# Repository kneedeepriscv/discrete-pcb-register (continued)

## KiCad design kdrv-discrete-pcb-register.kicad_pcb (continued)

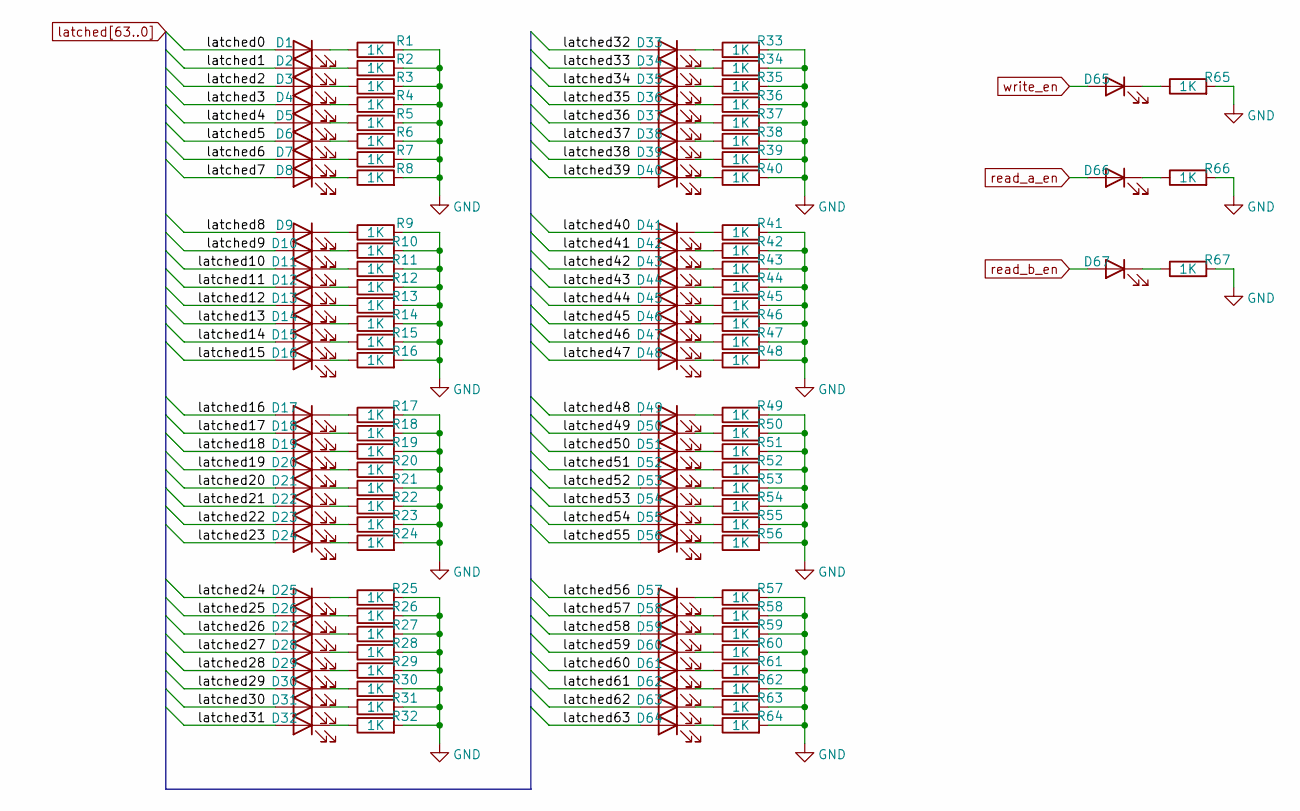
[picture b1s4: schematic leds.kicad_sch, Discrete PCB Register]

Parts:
D1: LED 0603 0605 0805 Right Angle Yellow Amber Green; LED_0805_2012Metric_Pad1.15x1.40mm_HandSolder
D2, D3, D4, D5, D6, D7, D8, D9, D10, D11, D12, D13, D14, D15, D16, D17, D18, D19, D20, D21, D22, D23, D24, D25, D26, D27, D28, D29, D30, D31, D32, D33, D34, D35, D36, D37, D38, D39, D40, D41, D42, D43, D44, D45, D46, D47, D48, D49, D50, D51, D52, D53, D54, D55, D56, D57, D58, D59, D60, D61, D62, D63, D64, D65, D66, D67: LED; LED_0805_2012Metric_Pad1.15x1.40mm_HandSolder
R1, R2, R3, R4, R5, R6, R7, R8, R9, R10, R11, R12, R13, R14, R15, R16, R17, R18, R19, R20, R21, R22, R23, R24, R25, R26, R27, R28, R29, R30, R31, R32, R33, R34, R35, R36, R37, R38, R39, R40, R41, R42, R43, R44, R45, R46, R47, R48, R49, R50, R51, R52, R53, R54, R55, R56, R57, R58, R59, R60, R61, R62, R63, R64, R65, R66, R67: 1K; R_0805_2012Metric_Pad1.20x1.40mm_HandSolder

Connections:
GND: R1.2, R2.2, R3.2, R4.2, R5.2, R6.2, R7.2, R8.2, R9.2, R10.2, R11.2, R12.2, R13.2, R14.2, R15.2, R16.2, R17.2, R18.2, R19.2, R20.2, R21.2, R22.2, R23.2, R24.2, R25.2, R26.2, R27.2, R28.2, R29.2, R30.2, R31.2, R32.2, R33.2, R34.2, R35.2, R36.2, R37.2, R38.2, R39.2, R40.2, R41.2, R42.2, R43.2, R44.2, R45.2, R46.2, R47.2, R48.2, R49.2, R50.2, R51.2, R52.2, R53.2, R54.2, R55.2, R56.2, R57.2, R58.2, R59.2, R60.2, R61.2, R62.2, R63.2, R64.2, R65.2, R66.2, R67.2; also elsewhere on the board
unnamed: D1.1 (K), R1.1
unnamed: D2.1 (K), R2.1
unnamed: D3.1 (K), R3.1
unnamed: D4.1 (K), R4.1
unnamed: D5.1 (K), R5.1
unnamed: D6.1 (K), R6.1
unnamed: D7.1 (K), R7.1
unnamed: D8.1 (K), R8.1
unnamed: D9.1 (K), R9.1
unnamed: D10.1 (K), R10.1
unnamed: D11.1 (K), R11.1
unnamed: D12.1 (K), R12.1
unnamed: D13.1 (K), R13.1
unnamed: D14.1 (K), R14.1
unnamed: D15.1 (K), R15.1
unnamed: D16.1 (K), R16.1
unnamed: D17.1 (K), R17.1
unnamed: D18.1 (K), R18.1
unnamed: D19.1 (K), R19.1
unnamed: D20.1 (K), R20.1
unnamed: D21.1 (K), R21.1
unnamed: D22.1 (K), R22.1
unnamed: D23.1 (K), R23.1
unnamed: D24.1 (K), R24.1
unnamed: D25.1 (K), R25.1
unnamed: D26.1 (K), R26.1
unnamed: D27.1 (K), R27.1
unnamed: D28.1 (K), R28.1
unnamed: D29.1 (K), R29.1
unnamed: D30.1 (K), R30.1
unnamed: D31.1 (K), R31.1
unnamed: D32.1 (K), R32.1
unnamed: D33.1 (K), R33.1
unnamed: D34.1 (K), R34.1
unnamed: D35.1 (K), R35.1
unnamed: D36.1 (K), R36.1
unnamed: D37.1 (K), R37.1
unnamed: D38.1 (K), R38.1
unnamed: D39.1 (K), R39.1
unnamed: D40.1 (K), R40.1
unnamed: D41.1 (K), R41.1
unnamed: D42.1 (K), R42.1
unnamed: D43.1 (K), R43.1
unnamed: D44.1 (K), R44.1
unnamed: D45.1 (K), R45.1
unnamed: D46.1 (K), R46.1
unnamed: D47.1 (K), R47.1
unnamed: D48.1 (K), R48.1
unnamed: D49.1 (K), R49.1
unnamed: D50.1 (K), R50.1
unnamed: D51.1 (K), R51.1
unnamed: D52.1 (K), R52.1
unnamed: D53.1 (K), R53.1
unnamed: D54.1 (K), R54.1
unnamed: D55.1 (K), R55.1
unnamed: D56.1 (K), R56.1
unnamed: D57.1 (K), R57.1
unnamed: D58.1 (K), R58.1
unnamed: D59.1 (K), R59.1
unnamed: D60.1 (K), R60.1
unnamed: D61.1 (K), R61.1
unnamed: D62.1 (K), R62.1
unnamed: D63.1 (K), R63.1
unnamed: D64.1 (K), R64.1
unnamed: D65.1 (K), R65.1
unnamed: D66.1 (K), R66.1
unnamed: D67.1 (K), R67.1
latched0: D1.2 (A); also elsewhere on the board
latched1: D2.2 (A); also elsewhere on the board
latched2: D3.2 (A); also elsewhere on the board
latched3: D4.2 (A); also elsewhere on the board
latched4: D5.2 (A); also elsewhere on the board
latched5: D6.2 (A); also elsewhere on the board
latched6: D7.2 (A); also elsewhere on the board
latched7: D8.2 (A); also elsewhere on the board
latched8: D9.2 (A); also elsewhere on the board
latched9: D10.2 (A); also elsewhere on the board
latched10: D11.2 (A); also elsewhere on the board
latched11: D12.2 (A); also elsewhere on the board
latched12: D13.2 (A); also elsewhere on the board
latched13: D14.2 (A); also elsewhere on the board
latched14: D15.2 (A); also elsewhere on the board
latched15: D16.2 (A); also elsewhere on the board
latched16: D17.2 (A); also elsewhere on the board
latched17: D18.2 (A); also elsewhere on the board
latched18: D19.2 (A); also elsewhere on the board
latched19: D20.2 (A); also elsewhere on the board
latched20: D21.2 (A); also elsewhere on the board
latched21: D22.2 (A); also elsewhere on the board
latched22: D23.2 (A); also elsewhere on the board
latched23: D24.2 (A); also elsewhere on the board
latched24: D25.2 (A); also elsewhere on the board
latched25: D26.2 (A); also elsewhere on the board
latched26: D27.2 (A); also elsewhere on the board
latched27: D28.2 (A); also elsewhere on the board
latched28: D29.2 (A); also elsewhere on the board
latched29: D30.2 (A); also elsewhere on the board
latched30: D31.2 (A); also elsewhere on the board
latched31: D32.2 (A); also elsewhere on the board
latched32: D33.2 (A); also elsewhere on the board
latched33: D34.2 (A); also elsewhere on the board
latched34: D35.2 (A); also elsewhere on the board
latched35: D36.2 (A); also elsewhere on the board
latched36: D37.2 (A); also elsewhere on the board
latched37: D38.2 (A); also elsewhere on the board
latched38: D39.2 (A); also elsewhere on the board
latched39: D40.2 (A); also elsewhere on the board
latched40: D41.2 (A); also elsewhere on the board
latched41: D42.2 (A); also elsewhere on the board
latched42: D43.2 (A); also elsewhere on the board
latched43: D44.2 (A); also elsewhere on the board
latched44: D45.2 (A); also elsewhere on the board
latched45: D46.2 (A); also elsewhere on the board
latched46: D47.2 (A); also elsewhere on the board
latched47: D48.2 (A); also elsewhere on the board
latched48: D49.2 (A); also elsewhere on the board
latched49: D50.2 (A); also elsewhere on the board
latched50: D51.2 (A); also elsewhere on the board
latched51: D52.2 (A); also elsewhere on the board
latched52: D53.2 (A); also elsewhere on the board
latched53: D54.2 (A); also elsewhere on the board
latched54: D55.2 (A); also elsewhere on the board
latched55: D56.2 (A); also elsewhere on the board
latched56: D57.2 (A); also elsewhere on the board
latched57: D58.2 (A); also elsewhere on the board
latched58: D59.2 (A); also elsewhere on the board
latched59: D60.2 (A); also elsewhere on the board
latched60: D61.2 (A); also elsewhere on the board
latched61: D62.2 (A); also elsewhere on the board
latched62: D63.2 (A); also elsewhere on the board
latched63: D64.2 (A); also elsewhere on the board
read_a_en: D66.2 (A); also elsewhere on the board
read_b_en: D67.2 (A); also elsewhere on the board
write_en: D65.2 (A); also elsewhere on the board

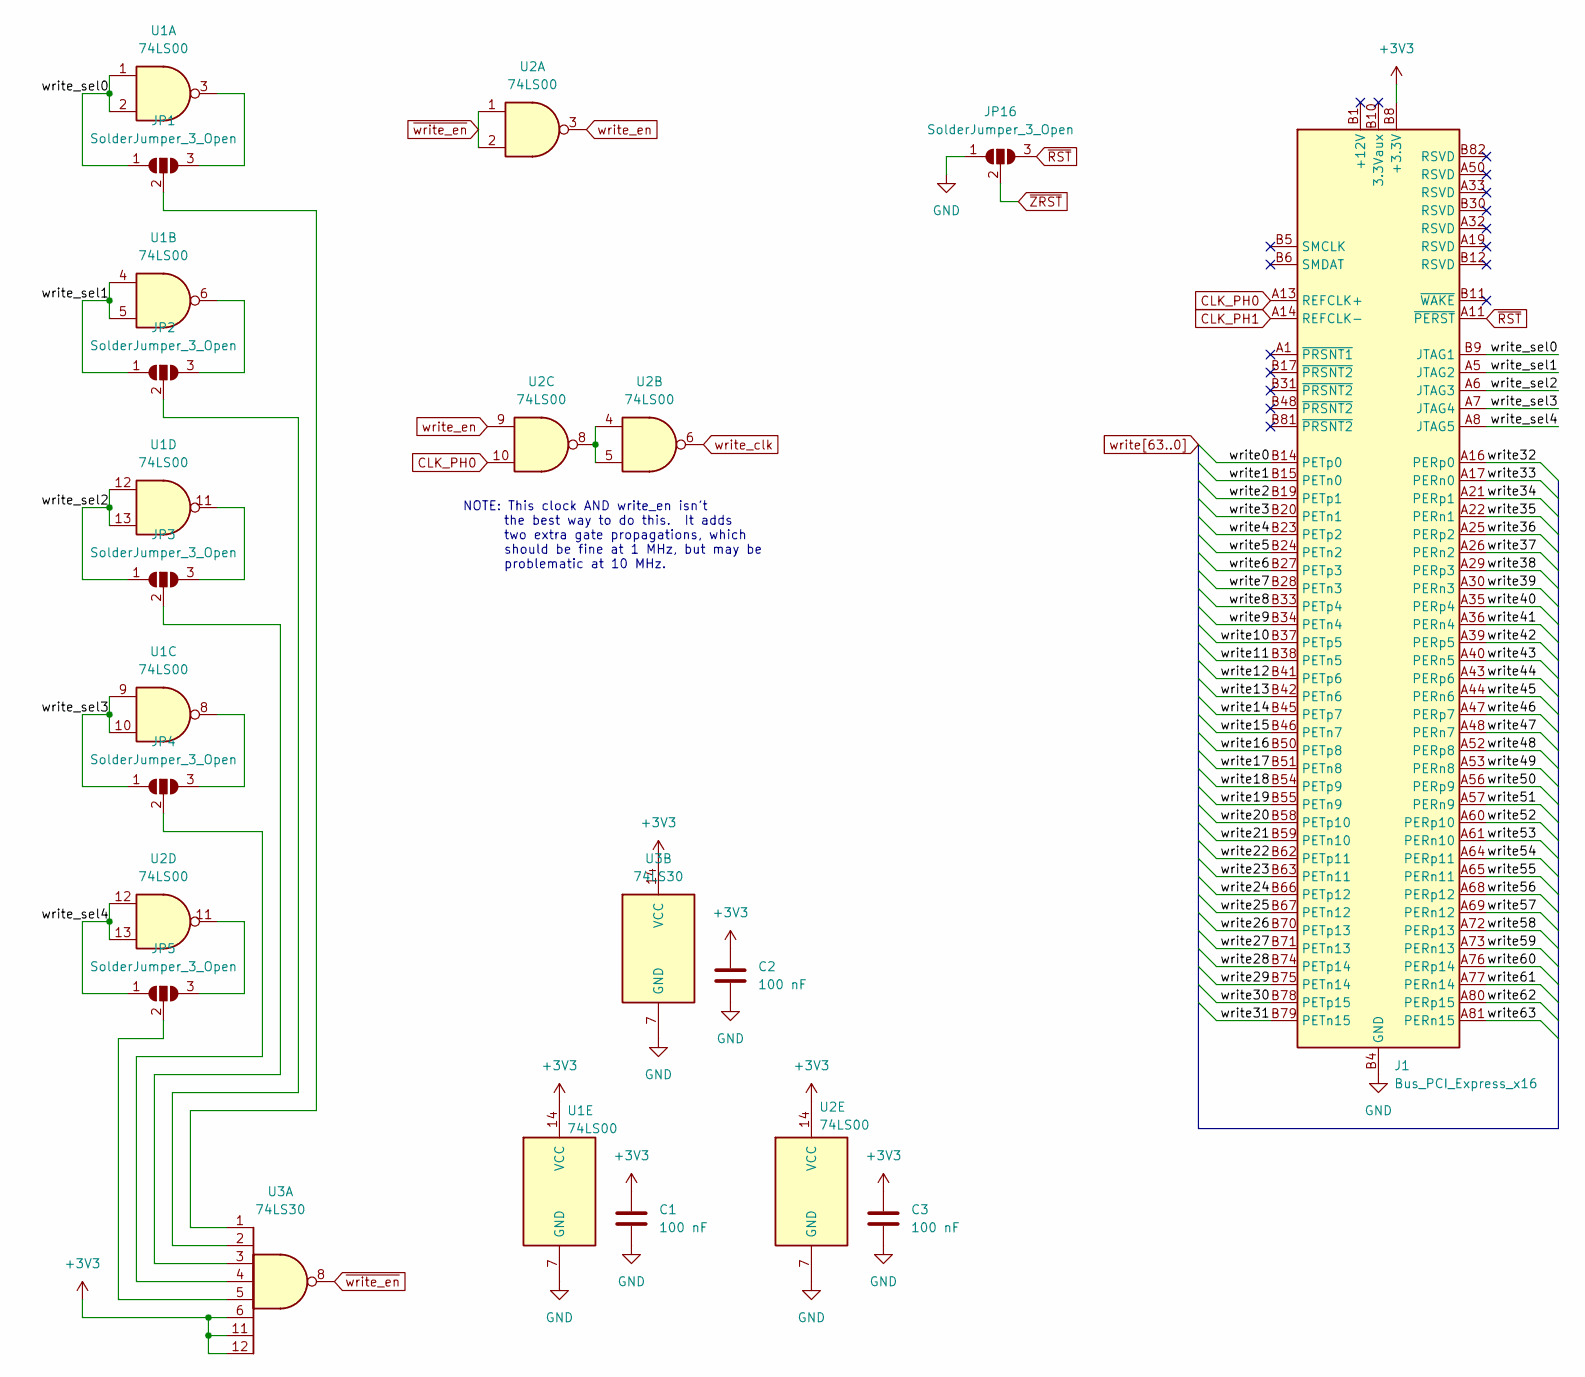
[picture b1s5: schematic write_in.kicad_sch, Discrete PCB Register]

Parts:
C1, C2, C3: 100 nF; C_0805_2012Metric_Pad1.18x1.45mm_HandSolder
J1: Bus_PCI_Express_x16; BUS_PCIexpress_x16
JP1, JP2, JP3, JP4, JP5, JP16: SolderJumper_3_Open; SolderJumper-3_P1.3mm_Open_RoundedPad1.0x1.5mm
U1, U2: 74LS00; SOIC-14_3.9x8.7mm_P1.27mm
U3: 74LS30; SOIC-14_3.9x8.7mm_P1.27mm

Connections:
+3V3: C1.1, C2.1, C3.1, J1.A9 (+3.3V), J1.A10 (+3.3V), J1.B8 (+3.3V), U1.14 (VCC), U2.14 (VCC), U3.6, U3.11, U3.12, U3.14 (VCC); also elsewhere on the board
/Write In/write_sel0: J1.B9 (JTAG1), JP1.1 (A), U1.1, U1.2
/Write In/write_sel1: J1.A5 (JTAG2), JP2.1 (A), U1.4, U1.5
/Write In/write_sel2: J1.A6 (JTAG3), JP3.1 (A), U1.12, U1.13
/Write In/write_sel3: J1.A7 (JTAG4), JP4.1 (A), U1.9, U1.10
/Write In/write_sel4: J1.A8 (JTAG5), JP5.1 (A), U2.12, U2.13
CLK_PH0: J1.A13 (REFCLK+), U2.10
CLK_PH1: J1.A14 (REFCLK-)
GND: C1.2, C2.2, C3.2, J1.A4 (GND), J1.A12 (GND), J1.A15 (GND), J1.A18 (GND), J1.A20 (GND), J1.A23 (GND), J1.A24 (GND), J1.A27 (GND), J1.A28 (GND), J1.A31 (GND), J1.A34 (GND), J1.A37 (GND), J1.A38 (GND), J1.A41 (GND), J1.A42 (GND), J1.A45 (GND), J1.A46 (GND), J1.A49 (GND), J1.A51 (GND), J1.A54 (GND), J1.A55 (GND), J1.A58 (GND), J1.A59 (GND), J1.A62 (GND), J1.A63 (GND), J1.A66 (GND), J1.A67 (GND), J1.A70 (GND), J1.A71 (GND), J1.A74 (GND), J1.A75 (GND), J1.A78 (GND), J1.A79 (GND), J1.A82 (GND), J1.B4 (GND), J1.B7 (GND), J1.B13 (GND), J1.B16 (GND), J1.B18 (GND), J1.B21 (GND), J1.B22 (GND), J1.B25 (GND), J1.B26 (GND), J1.B29 (GND), J1.B32 (GND), J1.B35 (GND), J1.B36 (GND), J1.B39 (GND), J1.B40 (GND), J1.B43 (GND), J1.B44 (GND), J1.B47 (GND), J1.B49 (GND), J1.B52 (GND), J1.B53 (GND), J1.B56 (GND), J1.B57 (GND), J1.B60 (GND), J1.B61 (GND), J1.B64 (GND), J1.B65 (GND), J1.B68 (GND), J1.B69 (GND), J1.B72 (GND), J1.B73 (GND), J1.B76 (GND), J1.B77 (GND), J1.B80 (GND), JP16.1 (A), U1.7 (GND), U2.7 (GND), U3.7 (GND); also elsewhere on the board
unnamed: JP1.3 (B), U1.3
unnamed: JP1.2 (C), U3.1
unnamed: JP2.3 (B), U1.6
unnamed: JP2.2 (C), U3.2
unnamed: JP3.3 (B), U1.11
unnamed: JP3.2 (C), U3.3
unnamed: JP4.3 (B), U1.8
unnamed: JP4.2 (C), U3.4
unnamed: JP5.3 (B), U2.11
unnamed: JP5.2 (C), U3.5
unnamed: U2.4, U2.5, U2.8
write0: J1.B14 (PETp0); also elsewhere on the board
write1: J1.B15 (PETn0); also elsewhere on the board
write2: J1.B19 (PETp1); also elsewhere on the board
write3: J1.B20 (PETn1); also elsewhere on the board
write4: J1.B23 (PETp2); also elsewhere on the board
write5: J1.B24 (PETn2); also elsewhere on the board
write6: J1.B27 (PETp3); also elsewhere on the board
write7: J1.B28 (PETn3); also elsewhere on the board
write8: J1.B33 (PETp4); also elsewhere on the board
write9: J1.B34 (PETn4); also elsewhere on the board
write10: J1.B37 (PETp5); also elsewhere on the board
write11: J1.B38 (PETn5); also elsewhere on the board
write12: J1.B41 (PETp6); also elsewhere on the board
write13: J1.B42 (PETn6); also elsewhere on the board
write14: J1.B45 (PETp7); also elsewhere on the board
write15: J1.B46 (PETn7); also elsewhere on the board
write16: J1.B50 (PETp8); also elsewhere on the board
write17: J1.B51 (PETn8); also elsewhere on the board
write18: J1.B54 (PETp9); also elsewhere on the board
write19: J1.B55 (PETn9); also elsewhere on the board
write20: J1.B58 (PETp10); also elsewhere on the board
write21: J1.B59 (PETn10); also elsewhere on the board
write22: J1.B62 (PETp11); also elsewhere on the board
write23: J1.B63 (PETn11); also elsewhere on the board
write24: J1.B66 (PETp12); also elsewhere on the board
write25: J1.B67 (PETn12); also elsewhere on the board
write26: J1.B70 (PETp13); also elsewhere on the board
write27: J1.B71 (PETn13); also elsewhere on the board
write28: J1.B74 (PETp14); also elsewhere on the board
write29: J1.B75 (PETn14); also elsewhere on the board
write30: J1.B78 (PETp15); also elsewhere on the board
write31: J1.B79 (PETn15); also elsewhere on the board
write32: J1.A16 (PERp0); also elsewhere on the board
write33: J1.A17 (PERn0); also elsewhere on the board
write34: J1.A21 (PERp1); also elsewhere on the board
write35: J1.A22 (PERn1); also elsewhere on the board
write36: J1.A25 (PERp2); also elsewhere on the board
write37: J1.A26 (PERn2); also elsewhere on the board
write38: J1.A29 (PERp3); also elsewhere on the board
write39: J1.A30 (PERn3); also elsewhere on the board
write40: J1.A35 (PERp4); also elsewhere on the board
write41: J1.A36 (PERn4); also elsewhere on the board
write42: J1.A39 (PERp5); also elsewhere on the board
write43: J1.A40 (PERn5); also elsewhere on the board
write44: J1.A43 (PERp6); also elsewhere on the board
write45: J1.A44 (PERn6); also elsewhere on the board
write46: J1.A47 (PERp7); also elsewhere on the board
write47: J1.A48 (PERn7); also elsewhere on the board
write48: J1.A52 (PERp8); also elsewhere on the board
write49: J1.A53 (PERn8); also elsewhere on the board
write50: J1.A56 (PERp9); also elsewhere on the board
write51: J1.A57 (PERn9); also elsewhere on the board
write52: J1.A60 (PERp10); also elsewhere on the board
write53: J1.A61 (PERn10); also elsewhere on the board
write54: J1.A64 (PERp11); also elsewhere on the board
write55: J1.A65 (PERn11); also elsewhere on the board
write56: J1.A68 (PERp12); also elsewhere on the board
write57: J1.A69 (PERn12); also elsewhere on the board
write58: J1.A72 (PERp13); also elsewhere on the board
write59: J1.A73 (PERn13); also elsewhere on the board
write60: J1.A76 (PERp14); also elsewhere on the board
write61: J1.A77 (PERn14); also elsewhere on the board
write62: J1.A80 (PERp15); also elsewhere on the board
write63: J1.A81 (PERn15); also elsewhere on the board
write_clk: U2.6; also elsewhere on the board
write_en: U2.3, U2.9; also elsewhere on the board
~RST: J1.A11 (~PERST), JP16.3 (B)
~ZRST: JP16.2 (C); also elsewhere on the board
~write_en: U2.1, U2.2, U3.8

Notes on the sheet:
NOTE: This clock AND write_en isn't the best way to do this. It adds two extra gate propagations, which should be fine at 1 MHz, but may be problematic at 10 MHz.

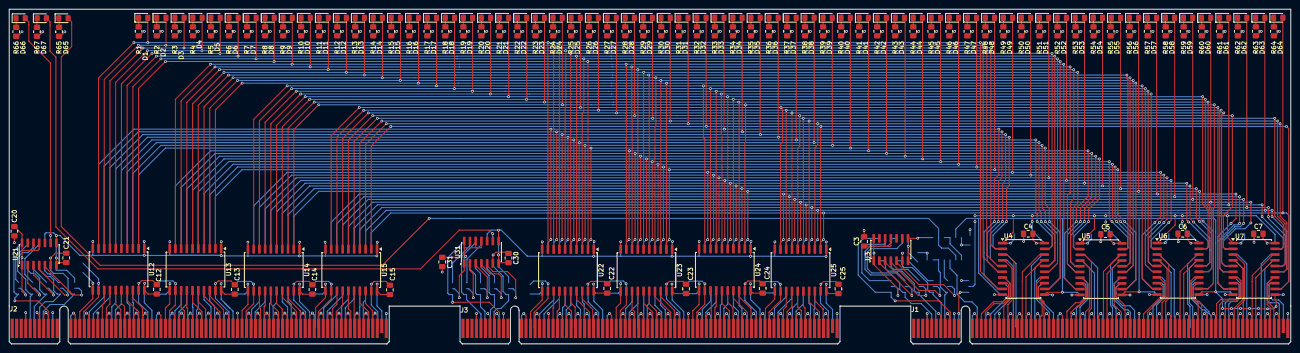
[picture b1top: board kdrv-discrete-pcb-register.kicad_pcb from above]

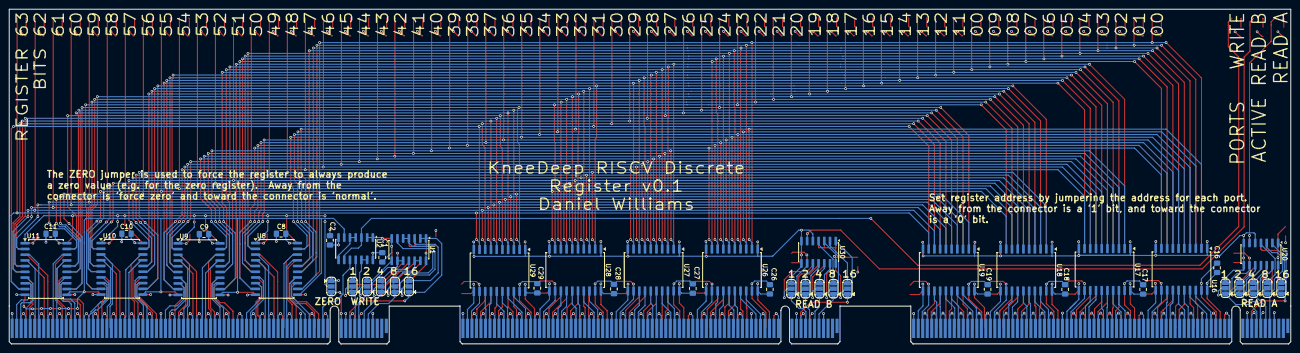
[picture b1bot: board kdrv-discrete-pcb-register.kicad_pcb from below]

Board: 4 copper layers, 284.3 x 74.2 mm, 215 parts (46 on the bottom side), 381 nets.

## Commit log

2026-02-12 Switching to the new KiCad gitignore base.
2026-02-12 Starting the connectors for the PCB.
2026-02-21 Schematic is pretty much complete.
2026-02-21 Current progress. Working on laying out the latched bus.
2026-02-21 More routing done.
2026-02-21 Read A Port mostly routed.
2026-02-21 Getting close to done with Read A Port.
2026-02-22 Progress on Read B Port.
2026-02-22 Moar progress. Working on the write in latch.
2026-02-24 Finished the register board layout. It's not as short as I would have liked, but it's done. 64 bit busses take an amount of space.
